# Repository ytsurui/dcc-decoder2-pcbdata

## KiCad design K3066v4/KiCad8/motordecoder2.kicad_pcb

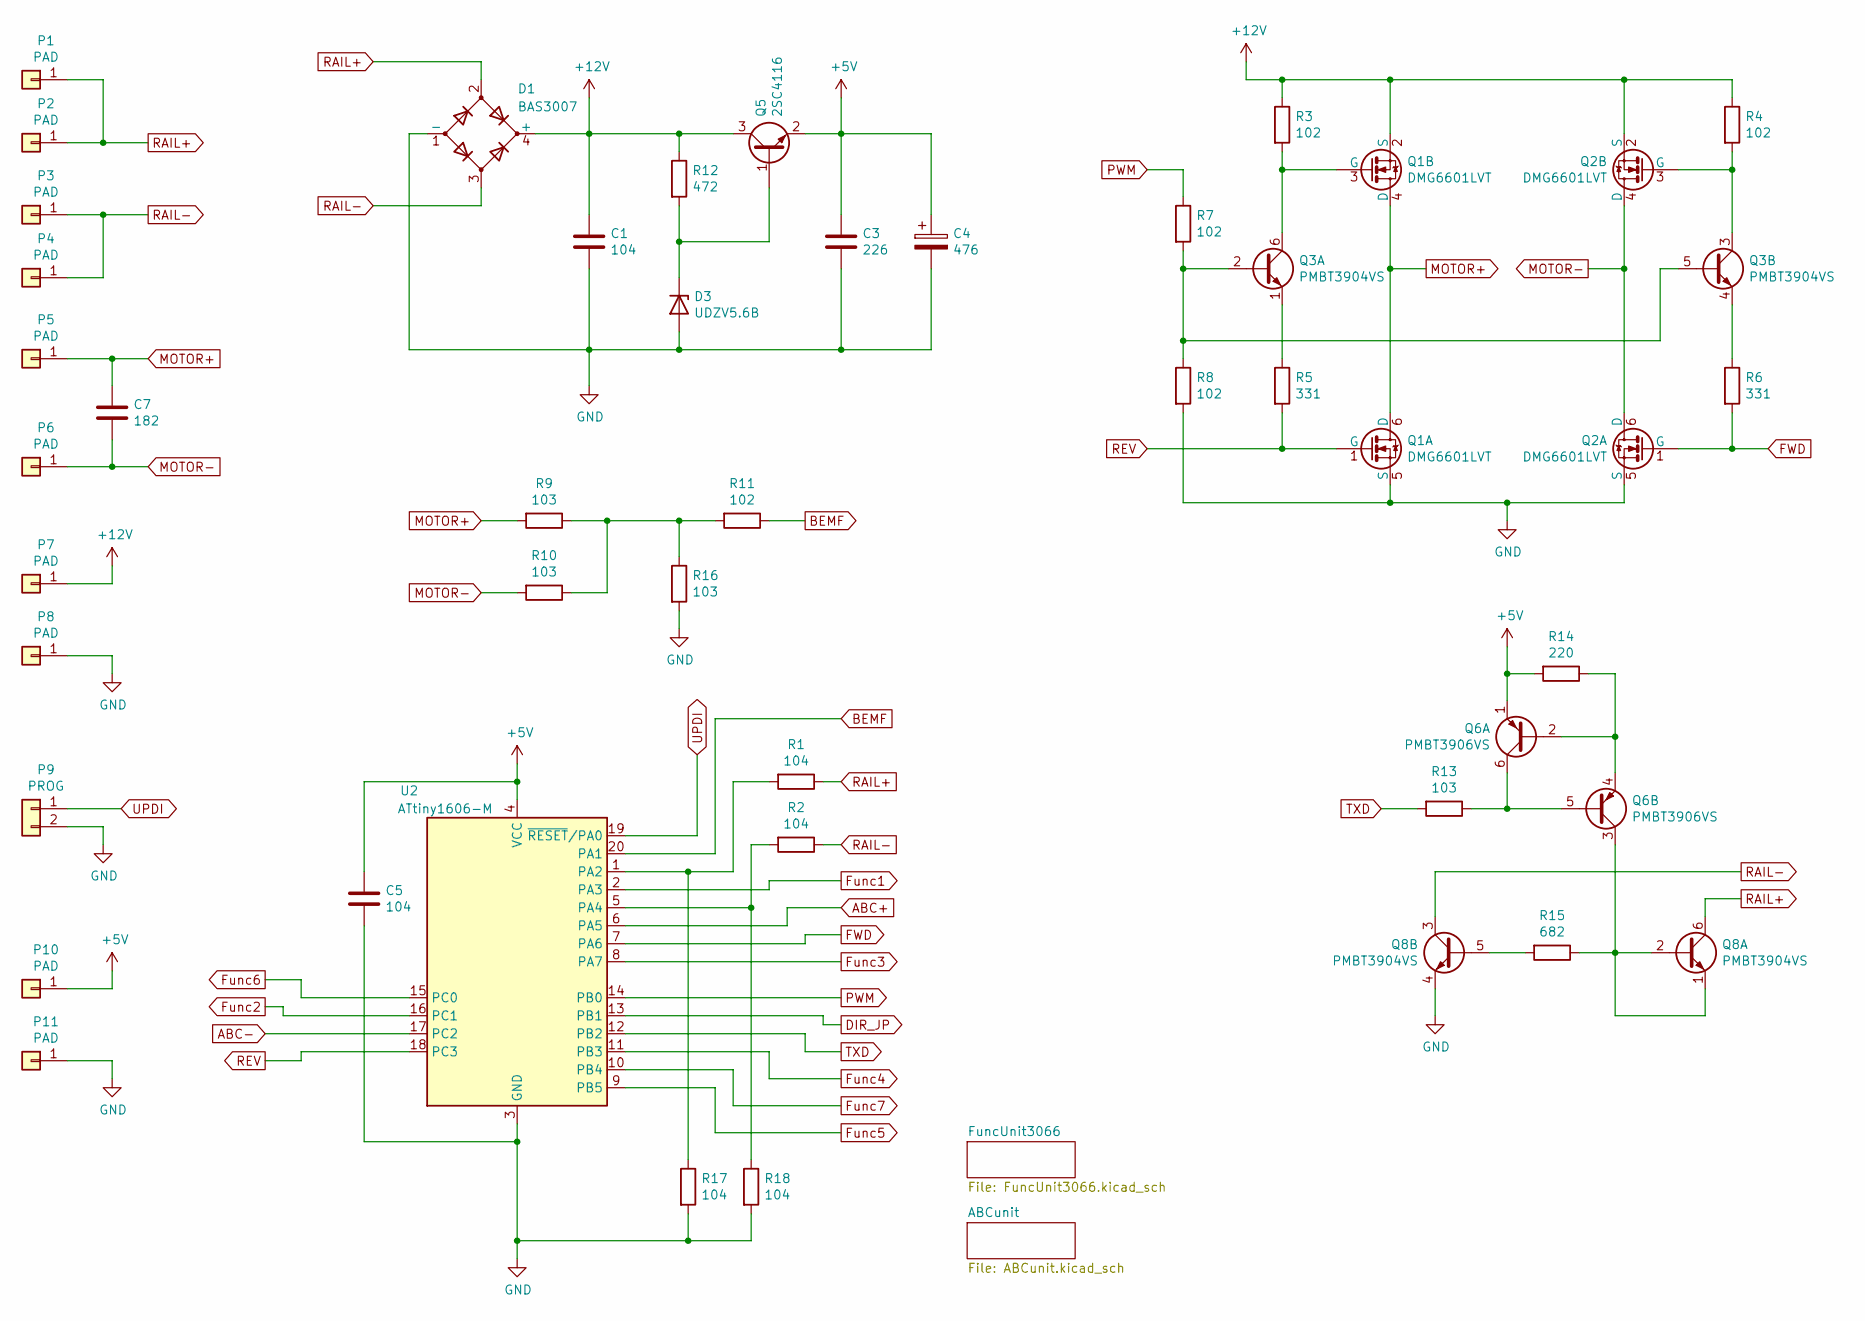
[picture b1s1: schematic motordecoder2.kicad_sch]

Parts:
C1, C5: 104; C_1005_v4
C3: 226; C_1608
C4: 476; CP_1608
C7: 182; C_1005_widespace
D1: BAS3007; SOT-143
D3: UDZV5.6B; UMD2
P1: PAD; KATO_FRAMEPAD_3066_v3_Right
P2: PAD; KATO_FRAMEPAD_3066_back_Right
P3: PAD; KATO_FRAMEPAD_3066_v3_Left
P4: PAD; KATO_FRAMEPAD_3066_back_Left
P5, P6: PAD; KATO_MOTORPAD_3066
P7, P11: PAD; PAD_0.7x0.9_SMD
P8, P10: PAD; PAD_0.6x1.0_SMD
P9: PROG; PAD_PROG_2PIN_HOLE0.7
Q1, Q2: DMG6601LVT; SOT-23-6-wide
Q3, Q8: PMBT3904VS; SOT-666-nomark-v2
Q5: 2SC4116; SC-70_v2
Q6: PMBT3906VS; SOT-666-nomark-v2
R1, R2, R17, R18: 104; R_1005_20240411
R3, R4, R7, R8, R11: 102; R_1005_20240411
R5, R6: 331; R_1005_20240411
R9, R10, R13, R16: 103; R_1005_20240411
R12: 472; R_1005_20240411
R14: 220; R_1608_20240411
R15: 682; R_1005_20240411
U2: ATtiny1606-M; VQFN-20-1EP_3x3mm_P0.4mm_EP1.7x1.7mm

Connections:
+5V: C3.1, C4.1, C5.1, P10.1, Q5.2 (E), Q6.1 (E1), R14.2, U2.4 (VCC)
+12V: C1.1, D1.4 (+), P7.1, Q1.2 (S), Q2.2 (S), Q5.3 (C), R3.1, R4.1, R12.1; also elsewhere on the board
ABC+: U2.6 (PA5); also elsewhere on the board
ABC-: U2.17 (PC2); also elsewhere on the board
BEMF: R11.1, U2.20 (PA1)
DIR_JP: U2.13 (PB1)
FWD: Q2.1 (G), R6.2, U2.7 (PA6)
Func1: U2.2 (PA3); also elsewhere on the board
Func2: U2.16 (PC1); also elsewhere on the board
Func3: U2.8 (PA7); also elsewhere on the board
Func4: U2.11 (PB3); also elsewhere on the board
Func5: U2.9 (PB5); also elsewhere on the board
Func6: U2.15 (PC0); also elsewhere on the board
Func7: U2.10 (PB4); also elsewhere on the board
GND: C1.2, C3.2, C4.2, C5.2, D1.1 (-), D3.2 (A), P8.1, P9.2, P11.1, Q1.5 (S), Q2.5 (S), Q8.4 (E2), R8.2, R16.2, R17.2, R18.2, U2.3 (GND), U2.21 (GND); also elsewhere on the board
MOTOR+: C7.1, P5.1, Q1.4 (D), Q1.6 (D), R9.2
MOTOR-: C7.2, P6.1, Q2.4 (D), Q2.6 (D), R10.2
unnamed: D3.1 (K), Q5.1 (B), R12.2
unnamed: Q1.3 (G), Q3.6 (C1), R3.2
unnamed: Q2.3 (G), Q3.3 (C2), R4.2
unnamed: Q3.2 (B1), Q3.5 (B2), R7.2, R8.1
unnamed: Q3.1 (E1), R5.1
unnamed: Q3.4 (E2), R6.1
unnamed: Q6.2 (B1), Q6.4 (E2), R14.1
unnamed: Q6.5 (B2), Q6.6 (C1), R13.1
unnamed: Q6.3 (C2), Q8.1 (E1), Q8.2 (B1), R15.1
unnamed: Q8.5 (B2), R15.2
unnamed: R9.1, R10.1, R11.2, R16.1
unnamed: R1.2, R17.1, U2.1 (PA2)
unnamed: R2.2, R18.1, U2.5 (PA4)
PWM: R7.1, U2.14 (PB0)
RAIL+: D1.2, P1.1, P2.1, Q8.6 (C1), R1.1; also elsewhere on the board
RAIL-: D1.3, P3.1, P4.1, Q8.3 (C2), R2.1; also elsewhere on the board
REV: Q1.1 (G), R5.2, U2.18 (PC3)
TXD: R13.2, U2.12 (PB2)
UPDI: P9.1, U2.19 (~RESET/PA0)

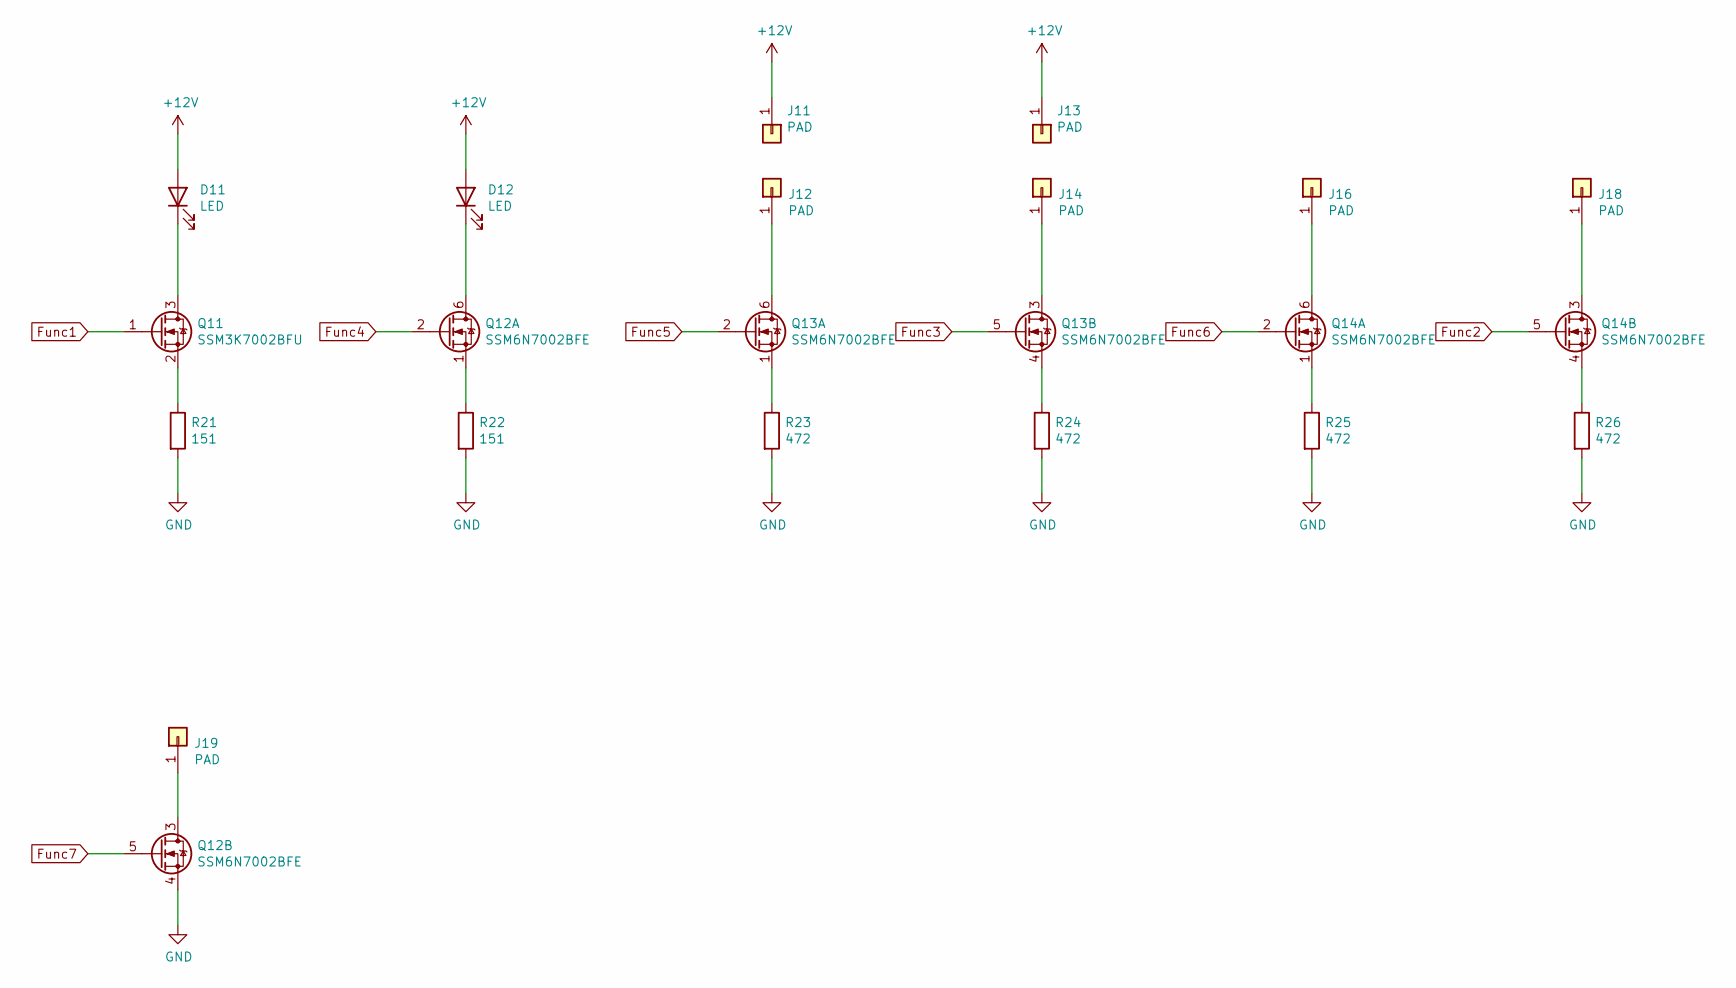
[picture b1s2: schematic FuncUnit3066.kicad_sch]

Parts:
D11, D12: LED; LED_1224_1005_SIDE_BIG2
J11: PAD; PAD_1.0x1.8_SMD
J12, J14, J16, J18: PAD; PAD_1.0x1.0_Hole0.6
J13, J19: PAD; PAD_0.6x1.0_SMD
Q11: SSM3K7002BFU; SC-70_v2
Q12, Q13, Q14: SSM6N7002BFE; SOT-666-nomark-v2
R21, R22: 151; R_1608_20240411
R23, R24, R25, R26: 472; R_1005_20240411

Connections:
+12V: D11.2 (A), D12.2 (A), J11.1, J13.1; also elsewhere on the board
Func1: Q11.1 (G); also elsewhere on the board
Func2: Q14.5 (G); also elsewhere on the board
Func3: Q13.5 (G); also elsewhere on the board
Func4: Q12.2 (G); also elsewhere on the board
Func5: Q13.2 (G); also elsewhere on the board
Func6: Q14.2 (G); also elsewhere on the board
Func7: Q12.5 (G); also elsewhere on the board
GND: Q12.4 (S), R21.2, R22.2, R23.2, R24.2, R25.2, R26.2; also elsewhere on the board
unnamed: D11.1 (K), Q11.3 (D)
unnamed: D12.1 (K), Q12.6 (D)
unnamed: J12.1, Q13.6 (D)
unnamed: J14.1, Q13.3 (D)
unnamed: J16.1, Q14.6 (D)
unnamed: J18.1, Q14.3 (D)
unnamed: J19.1, Q12.3 (D)
unnamed: Q11.2 (S), R21.1
unnamed: Q12.1 (S), R22.1
unnamed: Q13.1 (S), R23.1
unnamed: Q13.4 (S), R24.1
unnamed: Q14.1 (S), R25.1
unnamed: Q14.4 (S), R26.1

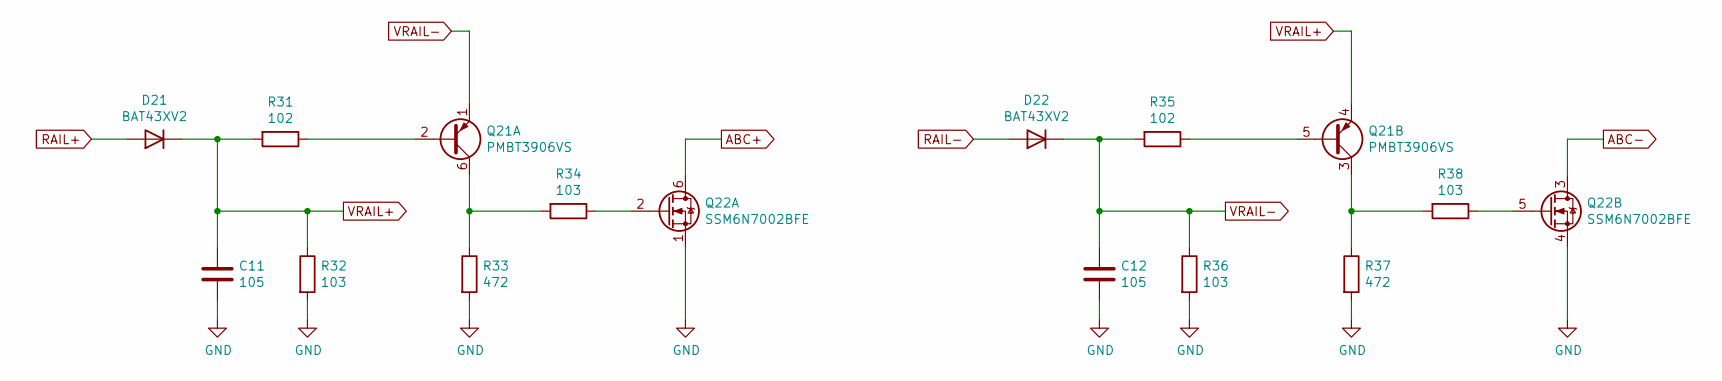
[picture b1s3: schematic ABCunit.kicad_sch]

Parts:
C11: 105; C_1005_widespace
C12: 105; C_1005_v4
D21: BAT43XV2; EMD2_small
D22: BAT43XV2; SOD-523
Q21: PMBT3906VS; SOT-666-nomark-v2
Q22: SSM6N7002BFE; SOT-666-nomark-v2
R31, R35: 102; R_1005_20240411
R32, R34, R36, R38: 103; R_1005_20240411
R33, R37: 472; R_1005_20240411

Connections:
ABC+: Q22.6 (D); also elsewhere on the board
ABC-: Q22.3 (D); also elsewhere on the board
GND: C11.2, C12.2, Q22.1 (S), Q22.4 (S), R32.2, R33.2, R36.2, R37.2; also elsewhere on the board
unnamed: Q21.2 (B1), R31.1
unnamed: Q21.6 (C1), R33.1, R34.2
unnamed: Q21.5 (B2), R35.1
unnamed: Q21.3 (C2), R37.1, R38.2
unnamed: Q22.2 (G), R34.1
unnamed: Q22.5 (G), R38.1
RAIL+: D21.2 (A); also elsewhere on the board
RAIL-: D22.2 (A); also elsewhere on the board
VRAIL+: C11.1, D21.1 (K), Q21.4 (E2), R31.2, R32.1
VRAIL-: C12.1, D22.1 (K), Q21.1 (E1), R35.2, R36.1

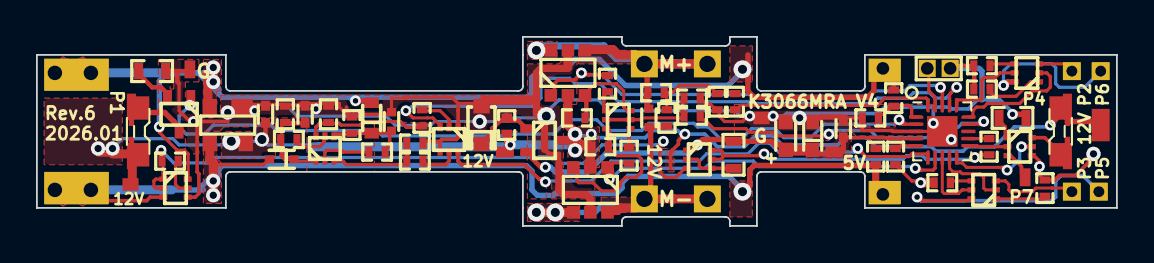
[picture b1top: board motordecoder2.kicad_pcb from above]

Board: 2 copper layers, 60.0 x 10.5 mm, 76 parts (0 on the bottom side), 56 nets.

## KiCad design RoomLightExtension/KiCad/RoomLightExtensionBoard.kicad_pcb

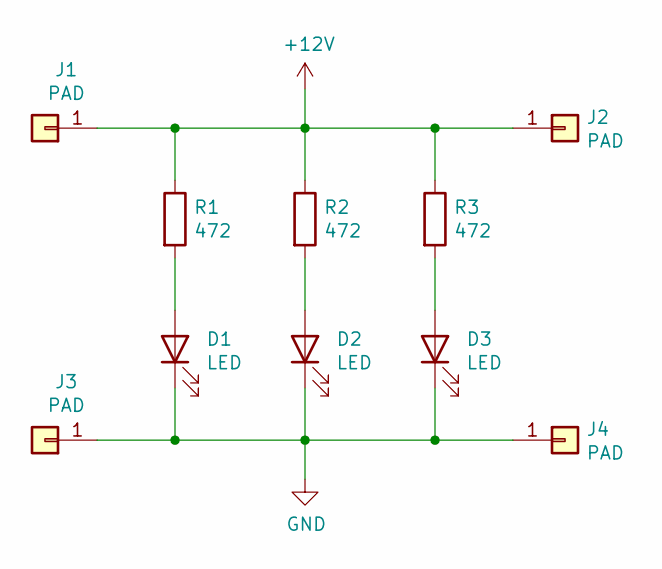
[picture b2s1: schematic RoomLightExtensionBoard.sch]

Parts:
D1, D2, D3: LED; LED_1608
J1, J2, J3, J4: PAD; PCB_CONN_PAD_2.5mmx1.2mm
R1, R2, R3: 472; R_1608_v2

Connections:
+12V: J1.1, J2.1, R1.1, R2.1, R3.1
GND: D1.1 (K), D2.1 (K), D3.1 (K), J3.1, J4.1
unnamed: D1.2 (A), R1.2
unnamed: D2.2 (A), R2.2
unnamed: D3.2 (A), R3.2

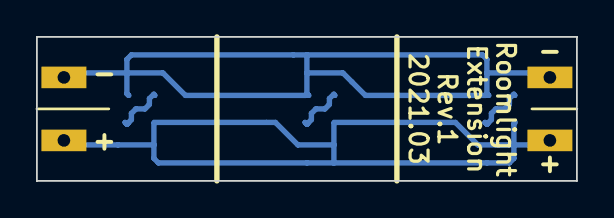
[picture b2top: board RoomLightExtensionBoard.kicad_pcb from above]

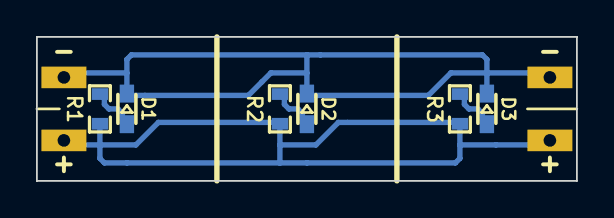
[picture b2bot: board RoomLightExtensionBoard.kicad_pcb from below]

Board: 2 copper layers, 30.0 x 8.0 mm, 10 parts (6 on the bottom side), 5 nets.
